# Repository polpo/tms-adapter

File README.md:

# TMS9x18 to TMS9x28 Adapter #

This is a PCB that will let you plug a TMS9128 or TMS9928 VDP, along with a [TMS-RGB](https://tms-rgb.com/), into a system that uses a TMS9118 or TMS9918 VDP. Such systems include numerous MSX computers, the NABU, and the TI 99/4A.

The adapter is intended to go in the sandwich of: TMS9x28 - socket - TMS-RGB - adapter - pin headers - socket - system motherboard.

There are two versions of the adapter, one for the TMS9128 and one for the TMS9928:

The TMS9128 adapter:

- Moves the TMS9128 CPUCLK signal from pin 37 to pin 38, where it is on the TMS9118.
- Adds 470 ohm load resistors on the Y, R-Y, and B-Y pins as there is no connection to the motherboard on this adapter for those pins. These resistors are required as per the TMS9128 datasheet.

The TMS9928 adapter:

- Creates a TTL clock signal from a crystal on the TMS9918 XTAL pins, divides it by 3 and outputs it on pin 38 (CPUCLK).
- Adds 470 ohm load resistors on the Y, R-Y, and B-Y pins as there is no connection to the motherboard on this adapter for those pins. These resistors are required as per the TMS9128 datasheet.

## Rationale ##

I have a Sony HB-101 "HitBit Mezzo" MSX computer that uses the relatively rare TMS9118 VDP. This is the variant that has composite output and supports 16Kx4 video RAM chips. Adding RGB output to systems using these TI VDPs is possible with the TMS-RGB project, but it requires using a VDP with component video output. For systems that use the TMS9118 VDP, a TMS9128 is a close match but the CPUCLK pin is in a different location. My HB-101 requires CPUCLK, so relocating the CPUCLK pinn is necessary. While it is possible to directly install a TMS9128 and relocate CPUCLK by cutting the clock trace on the PCB, this particular MSX is rare and valuable and I want the system to be as close to original as possible.

Later I got a NABU PC which uses the TMS9128A VDP and was tired of the composite output, so I adapted my original design to add a clock divider circuit to generate the CPUCLK output that the TMS9928 does not.

## Making the board ##

Depending on which version of the board you want, submit the gerbers under the gerbers-9918/ or gerbers-9928/ directory to your favorite PCB manufacturer. I have made mine at [OSH Park](https://oshpark.com) and [JLCPCB](https://jlcpcb.com).

For the TMS9128 version, a BOM is in the [bom-9128.csv](bom-9128.csv) file, consisting of:

- Low-profile machine pin headers, used to connect this adapter to the socket on the system motherboard
- 40-pin machine pin sockets for the TMS9128 and the system motherboard
- 3x 470 ohm 1% 1/4W 1206 SMT capacitors

TMS9x28 chips are available on the used market from eBay, AliExpress, UTSource, etc.

## Assembling the adapter ##

The assembly process is the same for both versions of the adapter. The photos in this guide are for the TMS9128 version but the TMS9928 version is assembled in the same way.

### 1. Prepare the TMS-RGB ###

The TMS-RGB will have to fit flush under the socket that the TMS9128 will plug into, meaning the holes in the TMS-RGB will have to fit over the larger diameter tops of the socket's machine pins. The plated pads that the TMS-RGB uses for its signals are large enough for this, but the un-plated holes are just a bit too small. Use a pin vise with a small diameter drill bit to enlarge the un-plated holes by hand. The PCB should cut easily so a power drill is not necessary! Be *very careful* to not drill holes large enough to come into contact with the ground plane on the TMS-RGB. The ground plane hugs these un-plated holes closely, and if the pins of the TMS9128 are shorted to ground, things will not work!

### 2. Solder the TMS-RGB to the socket ###

Place the TMS-RGB on the socket, ensuring it is flush and that pin 1 of the TMS-RGB, denoted by the square pad, is on the same end as the key notch of the socket. Solder the signal pads of the TMS-RGB to the pins of the socket.

### 3. Wire up the TMS-RGB and insulate ###

Connect the output wires of the TMS-RGB according to the [connection diagram for your choice of output cable in the TMS-RGB installation guide](https://tms-rgb.com/guideOutput.html). Insulate the top of the TMS-RGB with Kapton tape or some other thin insulator, as the top will be coming into close contact with the pin headers on the adapter.

### 4. Assemble the adapter ###

Solder all surface mount components to the adapter if you did not order it preassembled, then solder the machine pin headers. Then use a flush cutter to cut the tops of the protruding pins from the headers *as close as possible* to the top of the adapter PCB, being careful to not damage any traces. The tallest chip on the TMS-RGB, the LM1881, will be right up against these headers. and a large SMD capacitor will also be quite close, so it is important to make these as flush as possible.

### 5. Connect the adapter to the TMS-RGB + socket ###

Align the adapter to the TMS-RGB, being sure that the notch on the TMS-RGB's socket matches with the notch in the silkscreen on the adapter. This part is tricky – the pins of the socket should *just* be long enough to go through the holes in the adapter and be soldered. Keeping things level will be fiddly. I recommend tacking opposite corners while holding the assembly in your hands or in a small vise.

### 6. You're done! ###

Insert the TMS9x28 into the assembly, then place the assembly into the system's motherboard where the VDP should go. I recommend using a machine pin socket, but if height is an issue, you can solder directly into the motherboard.

## License ##

[The project license](LICENSE.txt) is under the CERN Open Hardware Licence Version 2 - Permissive.

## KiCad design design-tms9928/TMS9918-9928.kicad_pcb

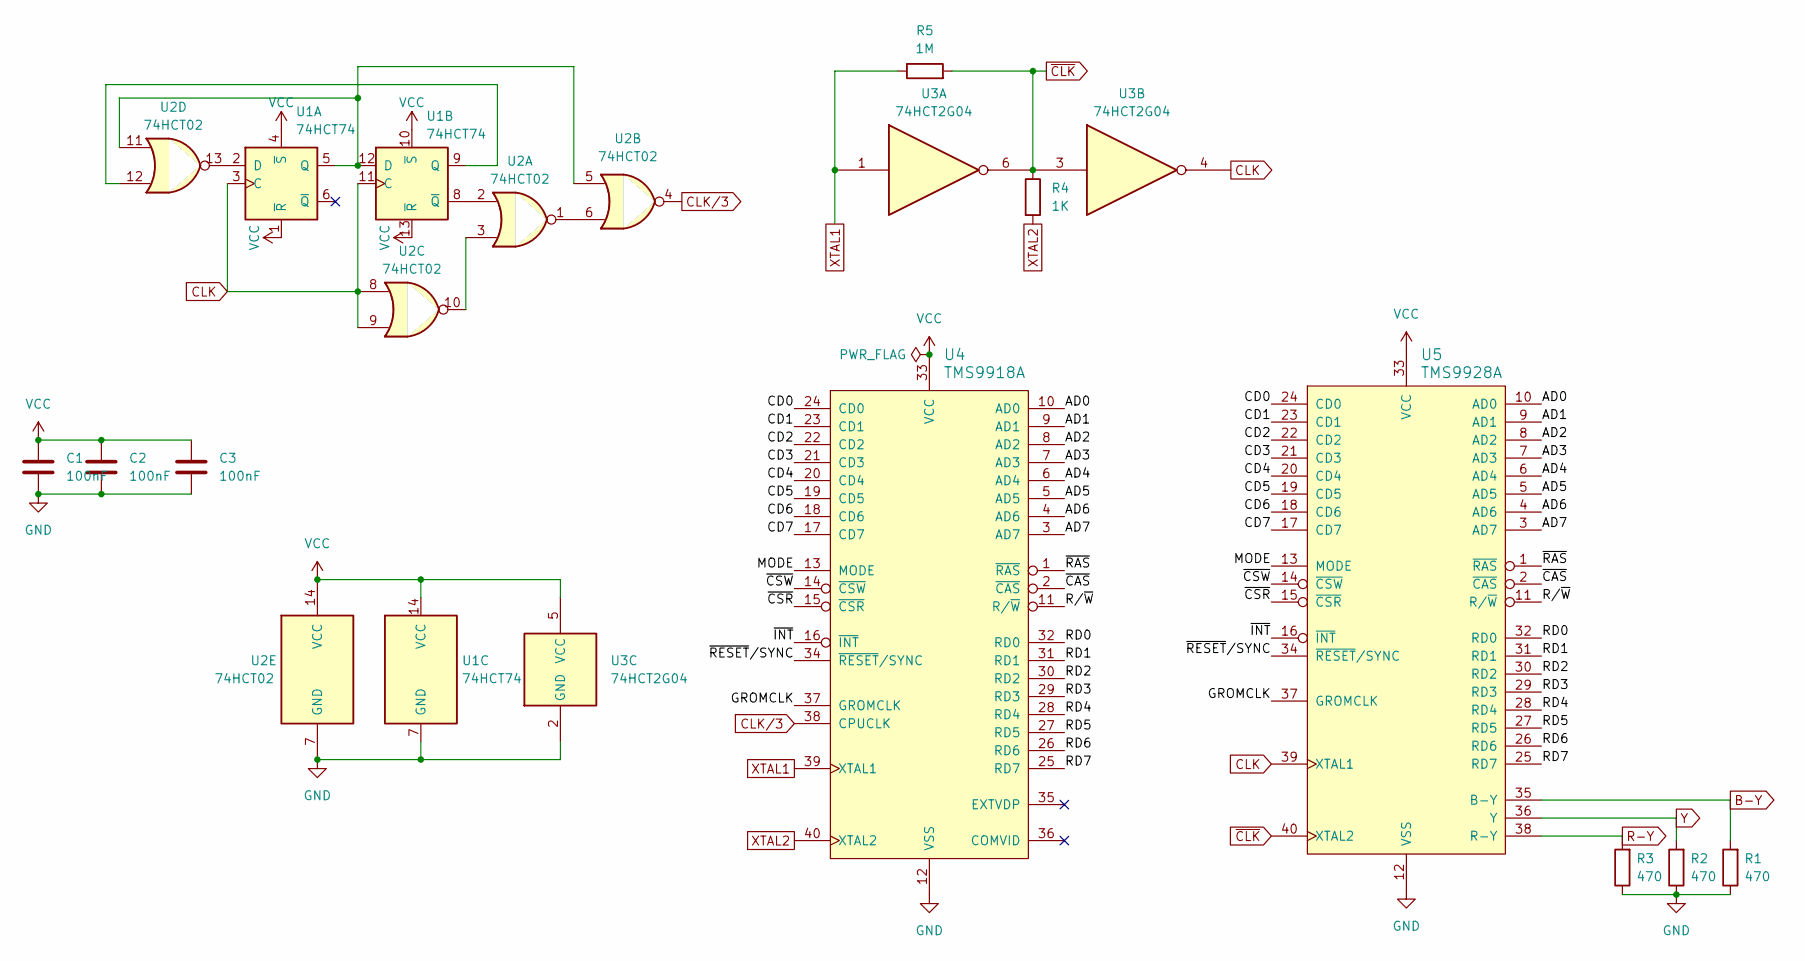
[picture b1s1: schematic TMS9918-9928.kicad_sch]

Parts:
C1, C2, C3: 100nF; C_0603_1608Metric
R1, R2, R3: 470; R_0603_1608Metric
R4: 1K; R_0603_1608Metric
R5: 1M; R_0603_1608Metric
U1: 74HCT74; TSSOP-14_4.4x5mm_P0.65mm
U2: 74HCT02; TSSOP-14_4.4x5mm_P0.65mm
U3: 74HCT2G04; TSOP-6_1.65x3.05mm_P0.95mm
U4: TMS9918A; DIP-40_W15.24mm_Socket
U5: TMS9928A; DIP-40_W15.24mm_Socket

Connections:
/AD0: U4.10 (AD0), U5.10 (AD0)
/AD1: U4.9 (AD1), U5.9 (AD1)
/AD2: U4.8 (AD2), U5.8 (AD2)
/AD3: U4.7 (AD3), U5.7 (AD3)
/AD4: U4.6 (AD4), U5.6 (AD4)
/AD5: U4.5 (AD5), U5.5 (AD5)
/AD6: U4.4 (AD6), U5.4 (AD6)
/AD7: U4.3 (AD7), U5.3 (AD7)
/CD0: U4.24 (CD0), U5.24 (CD0)
/CD1: U4.23 (CD1), U5.23 (CD1)
/CD2: U4.22 (CD2), U5.22 (CD2)
/CD3: U4.21 (CD3), U5.21 (CD3)
/CD4: U4.20 (CD4), U5.20 (CD4)
/CD5: U4.19 (CD5), U5.19 (CD5)
/CD6: U4.18 (CD6), U5.18 (CD6)
/CD7: U4.17 (CD7), U5.17 (CD7)
/GROMCLK: U4.37 (GROMCLK), U5.37 (GROMCLK)
/MODE: U4.13 (MODE), U5.13 (MODE)
/RD0: U4.32 (RD0), U5.32 (RD0)
/RD1: U4.31 (RD1), U5.31 (RD1)
/RD2: U4.30 (RD2), U5.30 (RD2)
/RD3: U4.29 (RD3), U5.29 (RD3)
/RD4: U4.28 (RD4), U5.28 (RD4)
/RD5: U4.27 (RD5), U5.27 (RD5)
/RD6: U4.26 (RD6), U5.26 (RD6)
/RD7: U4.25 (RD7), U5.25 (RD7)
/R/~W: U4.11 (R/~W), U5.11 (R/~W)
/~CAS: U4.2 (~CAS), U5.2 (~CAS)
/~CSR: U4.15 (~CSR), U5.15 (~CSR)
/~CSW: U4.14 (~CSW), U5.14 (~CSW)
/~INT: U4.16 (~INT), U5.16 (~INT)
/~RAS: U4.1 (~RAS), U5.1 (~RAS)
/~RESET/SYNC: U4.34 (~RESET/SYNC), U5.34 (~RESET/SYNC)
B-Y: R1.2, U5.35 (B-Y)
CLK: U1.3 (C), U1.11 (C), U2.8, U2.9, U3.4, U5.39 (XTAL1)
CLK/3: U2.4, U4.38 (CPUCLK)
GND: C1.2, C2.2, C3.2, R1.1, R2.1, R3.1, U1.7 (GND), U2.7 (GND), U3.2 (GND), U4.12 (VSS), U5.12 (VSS)
unnamed: U1.2 (D), U2.13
unnamed: U1.5 (Q), U1.12 (D), U2.5, U2.11
unnamed: U1.9 (Q), U2.12
unnamed: U1.8 (~Q), U2.2
unnamed: U2.1, U2.6
unnamed: U2.3, U2.10
R-Y: R3.2, U5.38 (R-Y)
VCC: C1.1, C2.1, C3.1, U1.1 (~R), U1.4 (~S), U1.10 (~S), U1.13 (~R), U1.14 (VCC), U2.14 (VCC), U3.5 (VCC), U4.33 (VCC), U5.33 (VCC)
XTAL1: R5.1, U3.1, U4.39 (XTAL1)
XTAL2: R4.2, U4.40 (XTAL2)
Y: R2.2, U5.36 (Y)
~CLK: R4.1, R5.2, U3.3, U3.6, U5.40 (XTAL2)

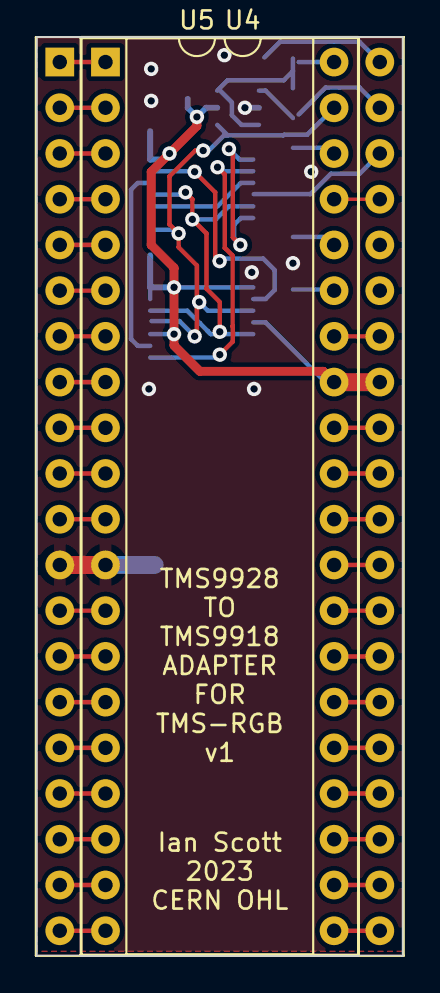
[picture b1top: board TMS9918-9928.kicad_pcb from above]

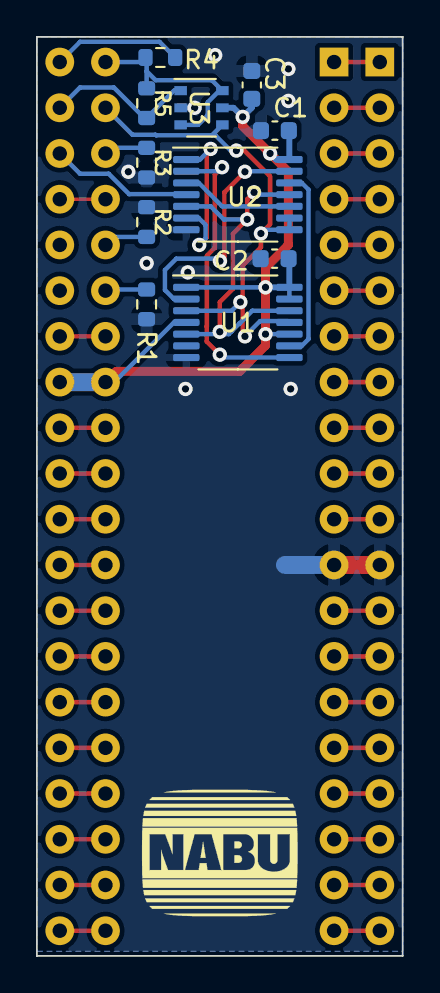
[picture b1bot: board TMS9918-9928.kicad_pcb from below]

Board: 2 copper layers, 20.3 x 51.1 mm, 13 parts (11 on the bottom side), 49 nets.

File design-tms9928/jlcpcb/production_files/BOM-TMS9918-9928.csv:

Comment,Designator,Footprint,LCSC
100nF,"C1,C2,C3",C_0603_1608Metric,C14663
1K,R4,R_0603_1608Metric,C21190
1M,R5,R_0603_1608Metric,C22935
470,"R1,R2,R3",R_0603_1608Metric,C23179
TMS9918A,U4,DIP-40_W15.24mm_Socket,
TMS9928A,U5,DIP-40_W15.24mm_Socket,
74HCT2G04,U3,TSOP-6_1.65x3.05mm_P0.95mm,
74HCT74,U1,TSSOP-14_4.4x5mm_P0.65mm,
74HCT02,U2,TSSOP-14_4.4x5mm_P0.65mm,

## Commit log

2022-03-08 Add images
2022-03-08 Update images
2022-03-08 Add assembly guide to README
2022-03-08 Add assembly guide to README (#1)
    * Add images
    * Add assembly guide to README
2022-03-08 More rationale in README
2022-03-08 Fix aspect radio on guide image
2022-03-08 Fix aspect ratio issues on mobile
2024-11-04 Add TMS9918 to TMS9928 adapter
2024-11-04 Rename original design dir
2024-11-04 Rearrange gerbers
2024-11-04 Rename bom
2024-11-04 Update README for TMS9928 version

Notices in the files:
design-tms9928/TMS9918-9928.kicad_pcb:
CERN OHL
